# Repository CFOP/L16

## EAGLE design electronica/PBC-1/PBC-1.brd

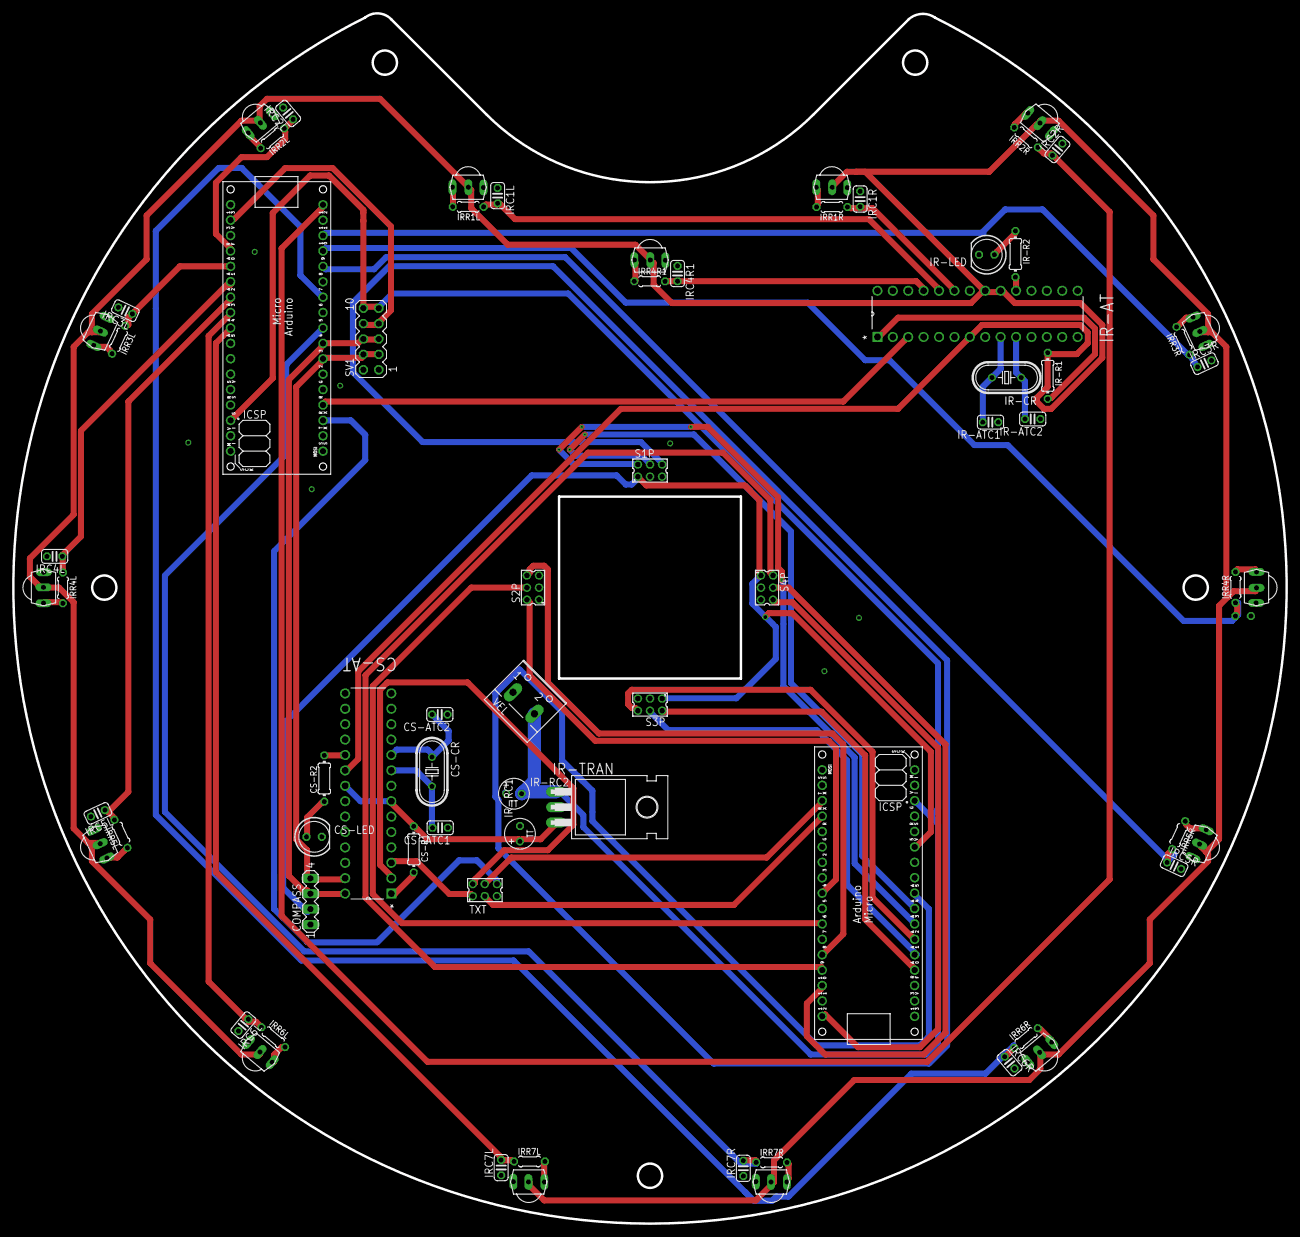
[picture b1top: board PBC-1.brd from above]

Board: 2 copper layers, 210.0 x 199.6 mm, 72 parts (1 on the bottom side), 65 nets.

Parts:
COMPASS: MA04-1
CS-AT: ATMEGA328P-PU; DIP254P762X457-28
CS-ATC1, CS-ATC2: 22 pF; C025-024X044
CS-CR: 16 MHz; HC49U70
CS-LED: LED5MM
CS-R1: 10k; 0204/7
CS-R2: 220; 0204/7
IR-AT: ATMEGA328P-PU; DIP254P762X457-28
IR-ATC1, IR-ATC2: 22 pF; C025-024X044
IR-CR: 16 MHz; HC49U70
IR-LED: LED5MM
IR-R1: 10k; 0204/7
IR-R2: 220; 0204/7
IR-RC1, IR-RC2: 10uf; TT2D5
IR-TRAN: 7805; TO220H
IRC1L, IRC1R, IRC2L, IRC2R, IRC3L, IRC3R, IRC4L, IRC4R, IRC4R1, IRC5L, IRC5R, IRC6L, IRC6R, IRC7L, IRC7R: C025-024X044
IRD1L, IRD1R, IRD2L, IRD2R, IRD3L, IRD4L, IRD4R, IRD5L, IRD5R, IRD6L, IRD6R, IRD7L, IRD7R: TSOP2240; TSOP18XX
IRD3R: TSOP1840; TSOP18XX
IRDP: TSOP2240; TSOP18XX
IRR1L, IRR1R, IRR2L, IRR2R, IRR3L, IRR3R, IRR4L, IRR4R, IRR4R1, IRR5L, IRR5R, IRR6L, IRR6R, IRR7L, IRR7R: 0204/5
PCB1, PCB3: ARDUINO_MICRO
S1P, S2P, S3P, S4P: 332-06
SV1: MA05-2
TXT: 87758-0616
VEL: W237-102

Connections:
+3V3: PCB3.3V3, SV1.7, SV1.8
+5V-IR: CS-AT.7, CS-AT.20, CS-AT.21, CS-R1.1, IR-AT.7, IR-AT.20, IR-AT.21, IR-R1.1, IR-RC1.+, IR-TRAN.3, IRD1L.VCC, IRD1R.VCC, IRD2L.VCC, IRD2R.VCC, IRD3L.VCC, IRD3R.VCC, IRD4L.VCC, IRD4R.VCC, IRD5L.VCC, IRD5R.VCC, IRD6L.VCC, IRD6R.VCC, IRD7L.VCC, IRD7R.VCC, IRDP.VCC
+5V-LT: COMPASS.2, PCB1.+5V, S1P.1, S3P.1, S4P.1
A0: PCB1.A0, S3P.2
A0IR: IRC7R.2, IRR7R.1, PCB3.D4
A1: PCB1.A1, S3P.4
A1IR: IRC6R.1, IRR6R.1, PCB3.D6
A2: PCB1.A2, S3P.6
A2IR: IRC5R.1, IRR5R.2, PCB3.D8
A3: PCB1.A3, S1P.2
A3IR: IRC4R.1, IRR4R.1, PCB3.D9
A4: PCB1.A4, S1P.4
A4IR: IRC3R.1, IRR3R.1, PCB3.D10
A5: PCB1.A5, S1P.6
A5IR: IRC2R.1, IRR2R.1, PCB3.D12
A6: PCB1.D4, S2P.2
A6IR: IRC2L.1, IRR2L.1, PCB3.A0
A7: PCB1.D6, S2P.4
A7IR: IRC3L.1, IRR3L.1, PCB3.A1
A8: PCB1.D8, S2P.6
A8IR: IRC4L.1, IRR4L.1, PCB3.A2
A9: PCB1.D9, S4P.2
A9IR: IRC5L.1, IRR5L.2, PCB3.A3
A10: PCB1.D10, S4P.4
A10IR: IRC6L.1, IRR6L.1, PCB3.A4
A11: PCB1.D12, S4P.6
A11IR: IRC7L.2, IRR7L.1, PCB3.A5
GND: COMPASS.1, CS-AT.8, CS-AT.22, CS-ATC1.1, CS-ATC2.1, CS-LED.K, IR-AT.8, IR-AT.22, IR-ATC1.1, IR-ATC2.1, IR-LED.K, IR-RC1.-, IR-RC2.+, IR-TRAN.2, IRC1L.1, IRC1R.1, IRC2L.2, IRC2R.2, IRC3L.2, IRC3R.2, IRC4L.2, IRC4R.2, IRC4R1.1, IRC5L.2, IRC5R.2, IRC6L.2, IRC6R.2, IRC7L.1, IRC7R.1, IRD1L.GND, IRD1R.GND, IRD2L.GND, IRD2R.GND, IRD3L.GND, IRD3R.GND, IRD4L.GND, IRD4R.GND, IRD5L.GND, IRD5R.GND, IRD6L.GND, IRD6R.GND, IRD7L.GND, IRD7R.GND, IRDP.GND, PCB1.GND, PCB1.GND., PCB3.GND, PCB3.GND., S1P.3, S1P.5, S2P.3, S2P.5, S3P.3, S3P.5, S4P.3, S4P.5, SV1.1, SV1.2, VEL.1
IR-CR: IR-AT.9, IR-ATC1.2, IR-CR.2
IRLOUT: IR-AT.24, IRC1L.2, IRR1L.1
IRPOUT: IR-AT.25, IRC4R1.2, IRR4R1.2
IRROUT: IR-AT.23, IRC1R.2, IRR1R.1
unnamed: IR-LED.A, IR-R2.1
unnamed: IR-AT.19, IR-R2.2
unnamed: IRD4R.OUT, IRR4R.2
unnamed: IRD7R.OUT, IRR7R.2
unnamed: IRD5R.OUT, IRR5R.1
unnamed: IRD2R.OUT, IRR2R.2
unnamed: IRD3R.OUT, IRR3R.2
unnamed: IRD1R.OUT, IRR1R.2
unnamed: IRD6R.OUT, IRR6R.2
unnamed: IRD3L.OUT, IRR3L.2
unnamed: IRD2L.OUT, IRR2L.2
unnamed: IRD1L.OUT, IRR1L.2
unnamed: IRD4L.OUT, IRR4L.2
unnamed: IRD5L.OUT, IRR5L.1
unnamed: IRD6L.OUT, IRR6L.2
unnamed: IRD7L.OUT, IRR7L.2
unnamed: IRDP.OUT, IRR4R1.1
unnamed: CS-LED.A, CS-R2.1
unnamed: CS-AT.19, CS-R2.2
PB6-A3: CS-AT.9, CS-ATC1.2, CS-CR.2
PB7-A1: IR-AT.10, IR-ATC2.2, IR-CR.1
PB7-A3: CS-AT.10, CS-ATC2.2, CS-CR.1
RESET-AT1: IR-AT.1, IR-R1.2
RESET-AT3: CS-AT.1, CS-R1.2
RX-CS: CS-AT.2, TXT.2
RX-LT: PCB1.RX1, TXT.3
SCL: COMPASS.3, CS-AT.28, PCB3.D3, SV1.5, SV1.6
SDA: COMPASS.4, CS-AT.27, PCB3.D2, SV1.3, SV1.4
TX-CS: CS-AT.3, TXT.1
TX-IR: PCB3.TX1, TXT.6
TX-IR2: IR-AT.3, PCB3.RX1
TX-LT: PCB1.TX1, TXT.4
VCC: IR-RC2.-, IR-TRAN.1, PCB1.VIN, PCB3.VIN, SV1.9, SV1.10, VEL.2

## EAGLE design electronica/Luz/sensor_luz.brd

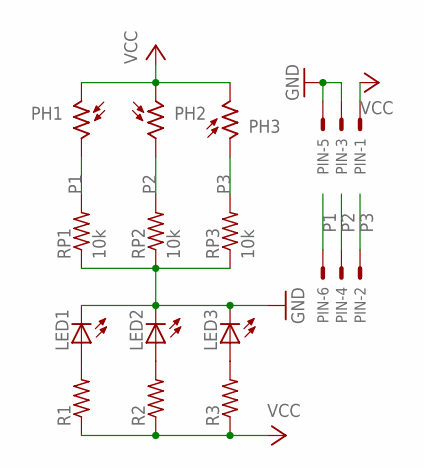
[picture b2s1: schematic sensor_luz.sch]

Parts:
LED1, LED2, LED3: LED3MM
PH1, PH2, PH3: VT20N4; TO46-VT200
PIN: 332-06
R1, R2, R3: R-US_0207/7; 0207/7
RP1, RP2, RP3: 10k; 0207/7

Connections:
GND: LED1.K (C), LED2.K (C), LED3.K (C), PIN.3, PIN.5, RP1.1, RP2.1, RP3.1
unnamed: LED1.A, R1.2
unnamed: LED2.A, R2.2
unnamed: LED3.A, R3.2
P1: PH1.2, PIN.6, RP1.2
P2: PH2.2, PIN.4, RP2.2
P3: PH3.1, PIN.2, RP3.2
VCC: PH1.1, PH2.1, PH3.2, PIN.1, R1.1, R2.1, R3.1

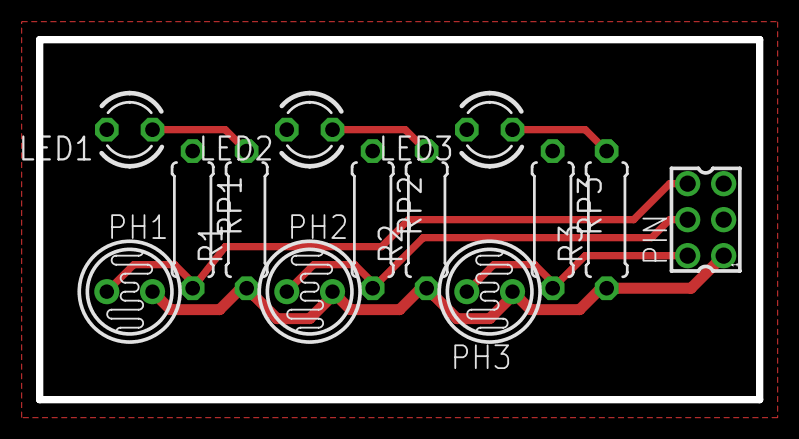
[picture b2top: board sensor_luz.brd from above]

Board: 2 copper layers, 40.0 x 20.0 mm, 13 parts (0 on the bottom side), 8 nets.

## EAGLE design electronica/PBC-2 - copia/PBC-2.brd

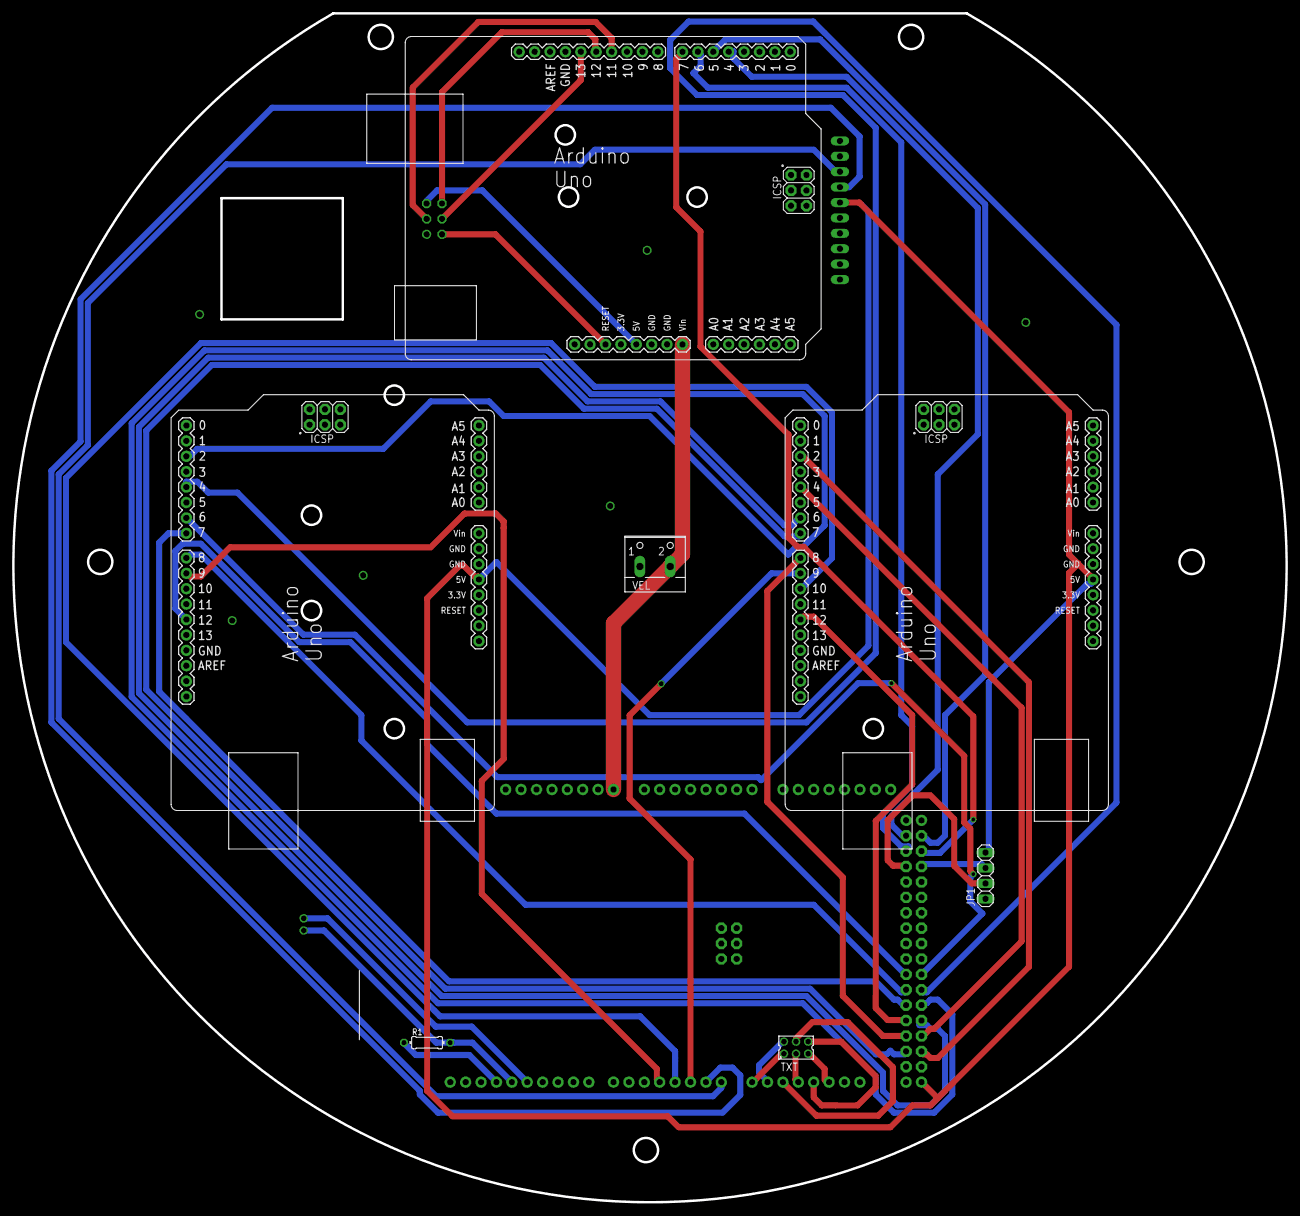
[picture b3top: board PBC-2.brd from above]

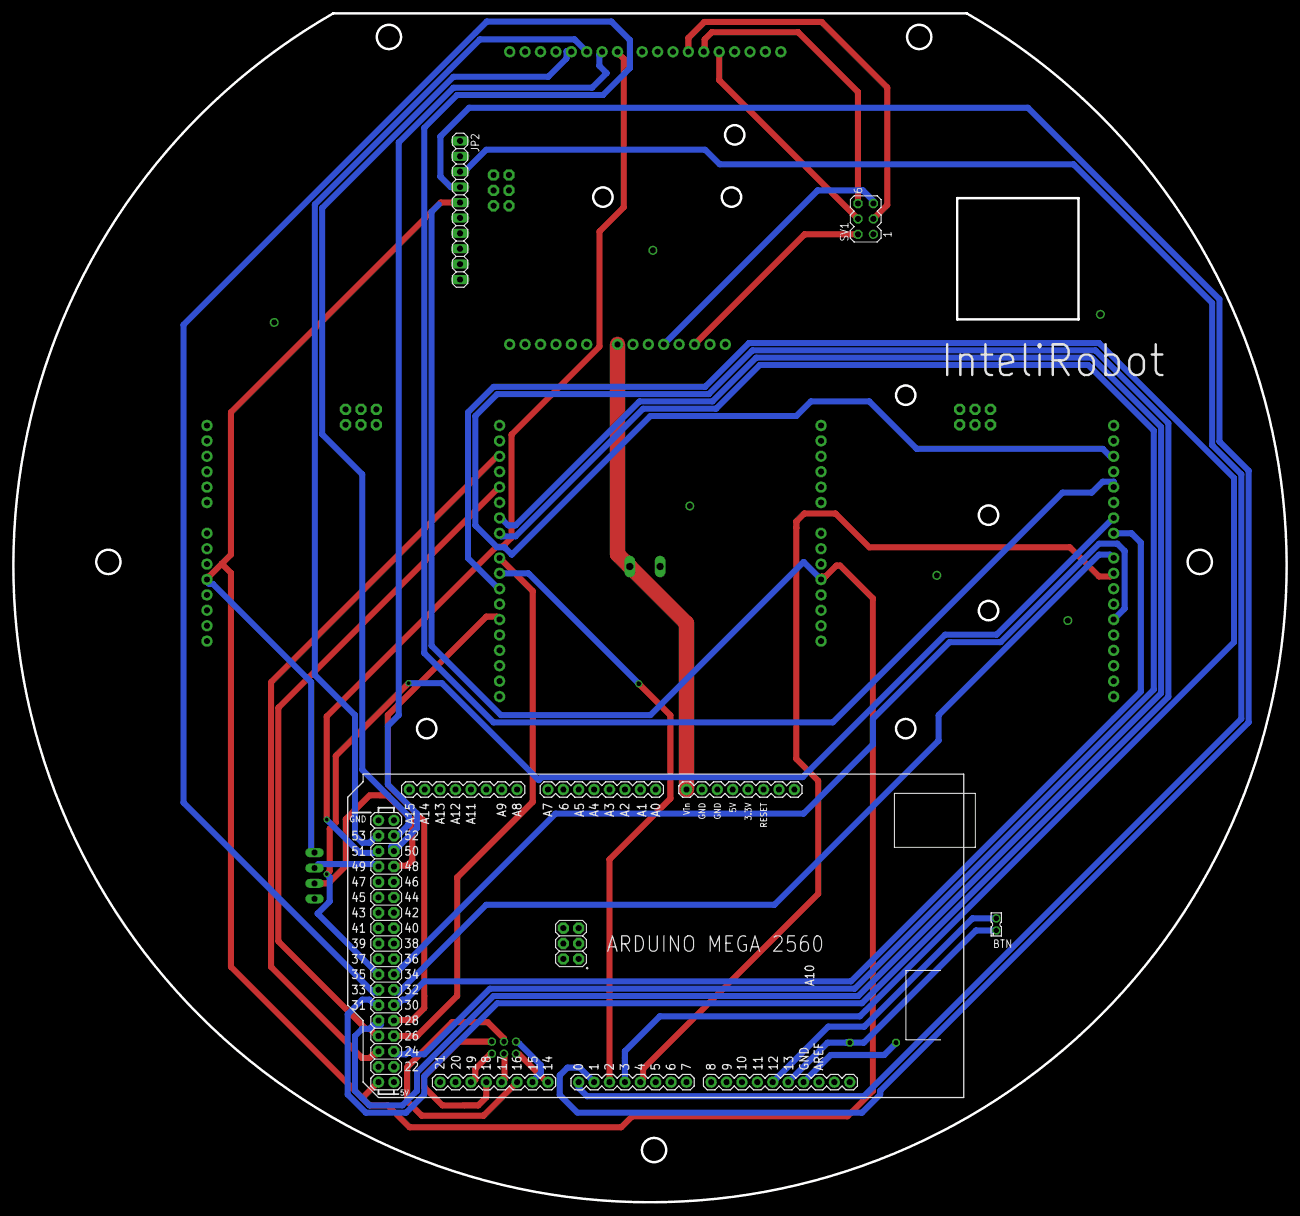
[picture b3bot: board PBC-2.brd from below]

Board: 2 copper layers, 210.0 x 196.1 mm, 11 parts (3 on the bottom side), 39 nets.

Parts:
BTN: 332-02
JP1: 1X04
JP2: 1X10
MEGA: ARDUINO_MEGA2560
PUENTE1, PUENTE2: ARDUINO_UNO
R1: 0204/7
SV1: MA03-2
TXT: 87758-0616
UNO: ARDUINO_UNO
VEL: W237-102

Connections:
+5V: JP1.4, JP2.5, MEGA.5V.., PUENTE1.5V, PUENTE2.5V
ECHO: JP1.2, MEGA.48
GND: JP1.1, JP2.7, MEGA.GND., MEGA.GND.., PUENTE1.GND, PUENTE1.GND., PUENTE1.GND.., PUENTE2.GND, PUENTE2.GND., PUENTE2.GND.., SV1.1, UNO.GND., UNO.GND.., VEL.1
M1ENL: MEGA.35, PUENTE2.6
M1ENR: MEGA.29, PUENTE1.6
M1INAL: MEGA.31, PUENTE2.2
M1INAR: MEGA.25, PUENTE1.2
M1INBL: MEGA.33, PUENTE2.4
M1INBR: MEGA.27, PUENTE1.4
M1PWML: MEGA.4, PUENTE2.9
M1PWMR: MEGA.2, PUENTE1.9
M2ENL: MEGA.34, PUENTE2.12
M2ENR: MEGA.28, PUENTE1.12
M2INAL: MEGA.30, PUENTE2.7
M2INAR: MEGA.24, PUENTE1.7
M2INBL: MEGA.32, PUENTE2.8
M2INBR: MEGA.26, PUENTE1.8
M2PWMR: MEGA.3, PUENTE1.10
MISO: SV1.6, UNO.12
MOSI: SV1.3, UNO.11
PIXY1: MEGA.51, UNO.7
PIXY2: MEGA.50, UNO.6
PIXY3: MEGA.53, UNO.5
PIXY4: MEGA.52, UNO.4
RESET: SV1.2, UNO.RESET
RX-CS: MEGA.15, TXT.2
RX-IR: MEGA.19, TXT.5
RX-LT: MEGA.17, TXT.3
S$1: BTN.2, MEGA.12
S$2: BTN.1, MEGA.13, R1.2
S$3: MEGA.GND, R1.1
SCK: SV1.4, UNO.13
TRIG: JP1.3, MEGA.49
TX-CS: MEGA.14, TXT.1
TX-IR: MEGA.18, TXT.6
TX-LT: MEGA.16, TXT.4
TX-XBEE: JP2.3, MEGA.0
V+: SV1.5, UNO.5V
VCC: MEGA.VIN, UNO.VIN, VEL.2

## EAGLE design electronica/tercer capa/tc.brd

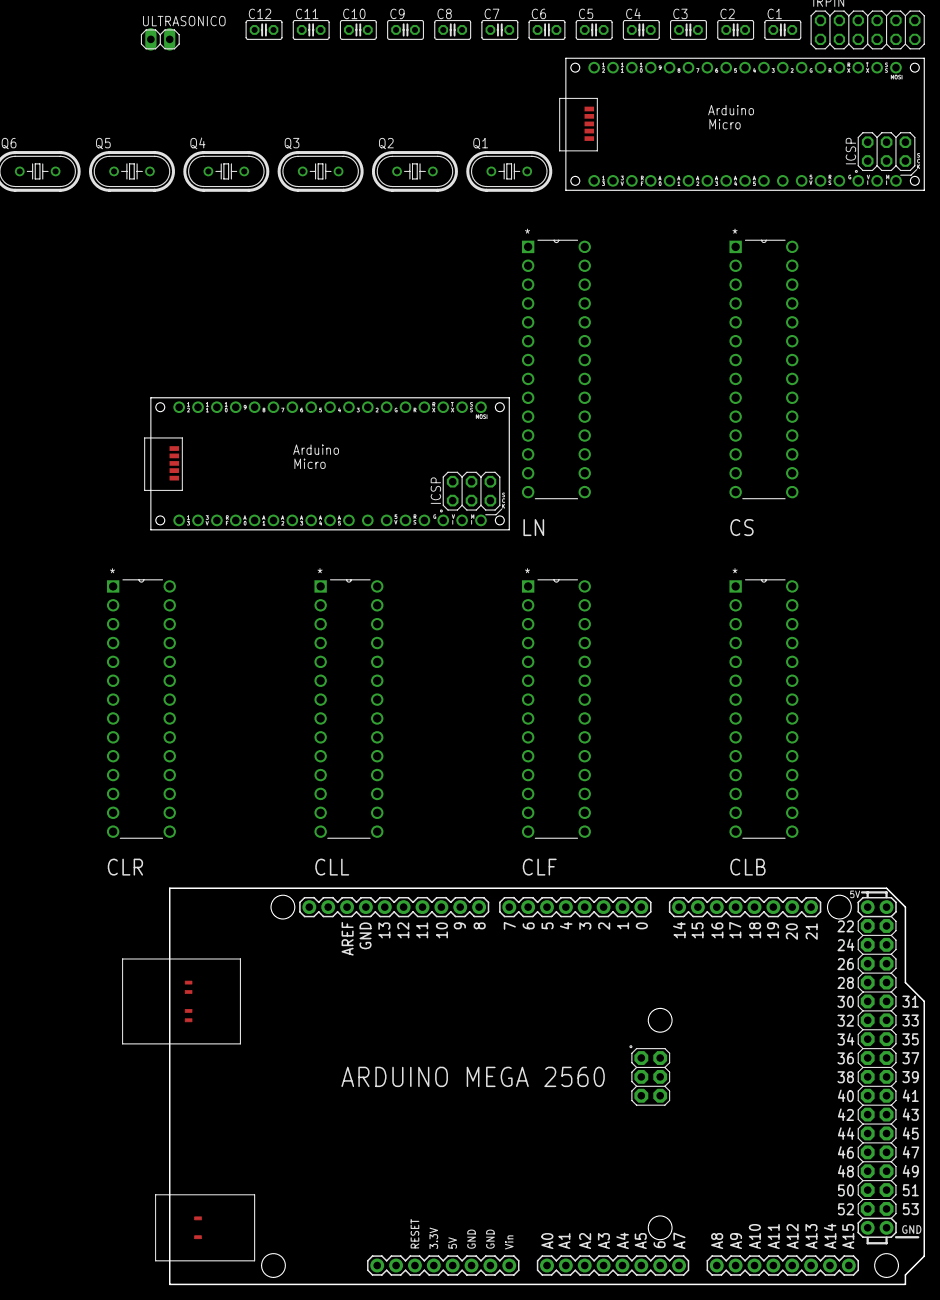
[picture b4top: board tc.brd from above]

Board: 2 copper layers, 29 parts (0 on the bottom side), 41 nets, no tracks yet.

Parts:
C1, C2, C3, C4, C5, C6, C7, C8, C9, C10, C11, C12: 22pF; C025-025X050
CLB: ATMEGA328P-PU; DIP254P762X457-28
CLF: ATMEGA328P-PU; DIP254P762X457-28
CLL: ATMEGA328P-PU; DIP254P762X457-28
CLR: ATMEGA328P-PU; DIP254P762X457-28
CS: ATMEGA328P-PU; DIP254P762X457-28
IR: ARDUINO_MICRO
IRPIN: 2X06
LN: ATMEGA328P-PU; DIP254P762X457-28
MASTER: ARDUINO_MEGA2560
PIXY: ARDUINO_MICRO
Q1, Q2, Q3, Q4, Q5, Q6: HC49U70
ULTRASONICO: 1X02

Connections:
+5V: CLB.7, CLB.20, CLF.7, CLF.20, CLL.7, CLL.20, CLR.7, CLR.20, CS.7, CS.20, LN.7, LN.20
GND: C1.1, C2.1, C3.1, C4.1, C5.1, C6.1, C7.1, C8.1, C9.1, C10.1, C11.1, C12.1, CLB.8, CLB.22, CLF.8, CLF.22, CLL.8, CLL.22, CLR.8, CLR.22, CS.8, CS.22, IR.GND, IR.GND., LN.8, LN.22, MASTER.GND, MASTER.GND., MASTER.GND.., PIXY.GND, PIXY.GND.
unnamed: CLL.10, Q1.2
unnamed: CLL.9, Q1.1
unnamed: CLB.10, Q4.2
unnamed: CLB.9, Q4.1
unnamed: CLR.10, Q3.2
unnamed: CLR.9, Q3.1
unnamed: CLF.10, Q2.2
unnamed: CLF.9, Q2.1
unnamed: LN.10, Q5.2
unnamed: LN.9, Q5.1
unnamed: CLL.15, LN.13
unnamed: CLB.18, LN.12
unnamed: CLF.18, LN.18
unnamed: CLR.16, LN.17
unnamed: PIXY.D12, ULTRASONICO.1
unnamed: PIXY.D11, ULTRASONICO.2
unnamed: C2.2, CS.10, Q6.2
unnamed: C1.2, CS.9, Q6.1
RX-CS: CS.2, MASTER.17
RX-IR: IR.RX1, MASTER.19
RX-LN: LN.2, MASTER.15
SCL: CLF.28, CLL.28, CS.28, IR.D3, LN.28, MASTER.SCL1, PIXY.D3
SDA: CLF.27, CLL.27, CS.27, IR.D2, LN.27, MASTER.SDA1, PIXY.D2
TSOP0: IR.A0, IRPIN.1
TSOP1: IR.A1, IRPIN.2
TSOP2: IR.A2, IRPIN.3
TSOP3: IR.A3, IRPIN.4
TSOP4: IR.A4, IRPIN.5
TSOP5: IR.A5, IRPIN.6
TSOP6: IR.D4, IRPIN.7
TSOP7: IR.D6, IRPIN.8
TSOP8: IR.D8, IRPIN.9
TSOP9: IR.D9, IRPIN.10
TSOP10: IR.D10, IRPIN.11
TSOP11: IR.D12, IRPIN.12
TX-CS: CS.3, MASTER.16
TX-IR: IR.TX1, MASTER.18
TX-LN: LN.3, MASTER.14
VCC: IR.VIN, MASTER.VIN, PIXY.VIN

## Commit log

2015-08-07 e-microcontroladores
    conexion microcontroladores
2015-08-07 tercer capa
    edicion equematico
2016-01-17 borrarCosasChafas
2016-01-17 electronica diagrama
    diagrama de sensor luz
2016-01-17 electronica diseño placa luz
    diseño de la placa del sensor de luz
2016-01-17 electronica diseño final luz
    diseño final en la placa del sensor de luz (agujeros para tornillos)
2016-01-17 electronica sensor luz
    ajustes finales
2016-01-17 electrinica Gerber sensor luz
    generar gerber del sensor de luz
2016-01-24 libreria de brujula
2016-01-24 Revert "libreria de brujula"
    This reverts commit 4eb655c5f50e373daa0fbc54ebfaa1261d1fb598.
2016-01-24 Revert "Revert "libreria de brujula""
    This reverts commit a7c683855eb38a8c1a28575e8b513ad2061d042a.
2016-01-26 sinc 1
2016-01-30 compass
    .cpp y .h
2016-02-01 PCB-|
    diseño de la placa de enmedio
2016-02-04 diagrama pcb2
    diagrama de la pcb de arriba y prueba de la comunicacion serial
2016-02-04 Prueba
    prueba del multiplexor
2016-02-06 posiciones pcb-2
2016-02-06 borro el rar
    se subio el rar .-.
2016-02-06 java PID
2016-02-08 MUX analogicos
2016-02-11 fin pcb-2
    fin pcb-2
2016-02-14 ELECTRONICA
    FIN DE LOS DISEÑOS
2016-02-15 Ángulos corregidos
2016-02-15 Estructura
2016-02-17 ELECTRONICA FIN
    diseño final de las pcb's y creacion de gerbers
2016-02-20 updt
    none
2016-02-22 MotorControllerTerminado
2016-02-22 CorreccionDePuertos
2016-02-27 UpdateC
2016-02-28 serialDevice
2016-02-28 libraries
    photoresistors and movements
2016-02-29 Photoresistor
    libreria compila
2016-02-29 photoresistor library
    Modificado, ya compila
2016-03-01 photoresistor library
    compila
2016-03-01 InfraredDetection and DirectionController
    InfraredDetection not finished and DirectionController.h modified
2016-03-01 nada
    ignorar
2016-03-02 InfraredDetection
    terminado,no probado
2016-03-02 Folders changed
    Cambio de nombre de carpetas
2016-03-02 Corrections
2016-03-02 SerialDeviceExample
2016-03-04 serial update
2016-03-05 InfraredDetection
    terminado ,no tiene comentarios
2016-03-05 correctedphotoresistor
2016-03-05 example
    porgramas para el programa final
2016-03-05 ignore
    ignorar
2016-03-09 Direction and photoresistor
    direction marca error.h ,no compila fotoresistencia vuelto a corregir
2016-03-09 MotorController Update
2016-03-09 MotorController Example
2016-03-12 Library Update
2016-03-12 final program
    funciones de movimientos
2016-03-14 Individual Photoresistor Calibration
2016-03-14 Serial Micro Device Library
2016-03-14 Serial Micro Device Update
